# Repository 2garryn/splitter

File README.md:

# Headphone splitter

## Parts

Capacitors:
 - 470uf 25V 10x10.2 [EEEHA1E471P from Panasonic] (http://industrial.panasonic.com/ww/products/capacitors/aluminum-capacitors/aluminum-cap-smd/ha-v/EEEHA1E471P)
 - 100uf 25V 6.3x7.7 [EEEFK1E101XP from Panasonic] (http://industrial.panasonic.com/ww/products/capacitors/aluminum-capacitors/aluminum-cap-smd/fk-v/EEEFK1E101XP)
 - 4.7uf >=16V 4x5.3 or 4x5.4

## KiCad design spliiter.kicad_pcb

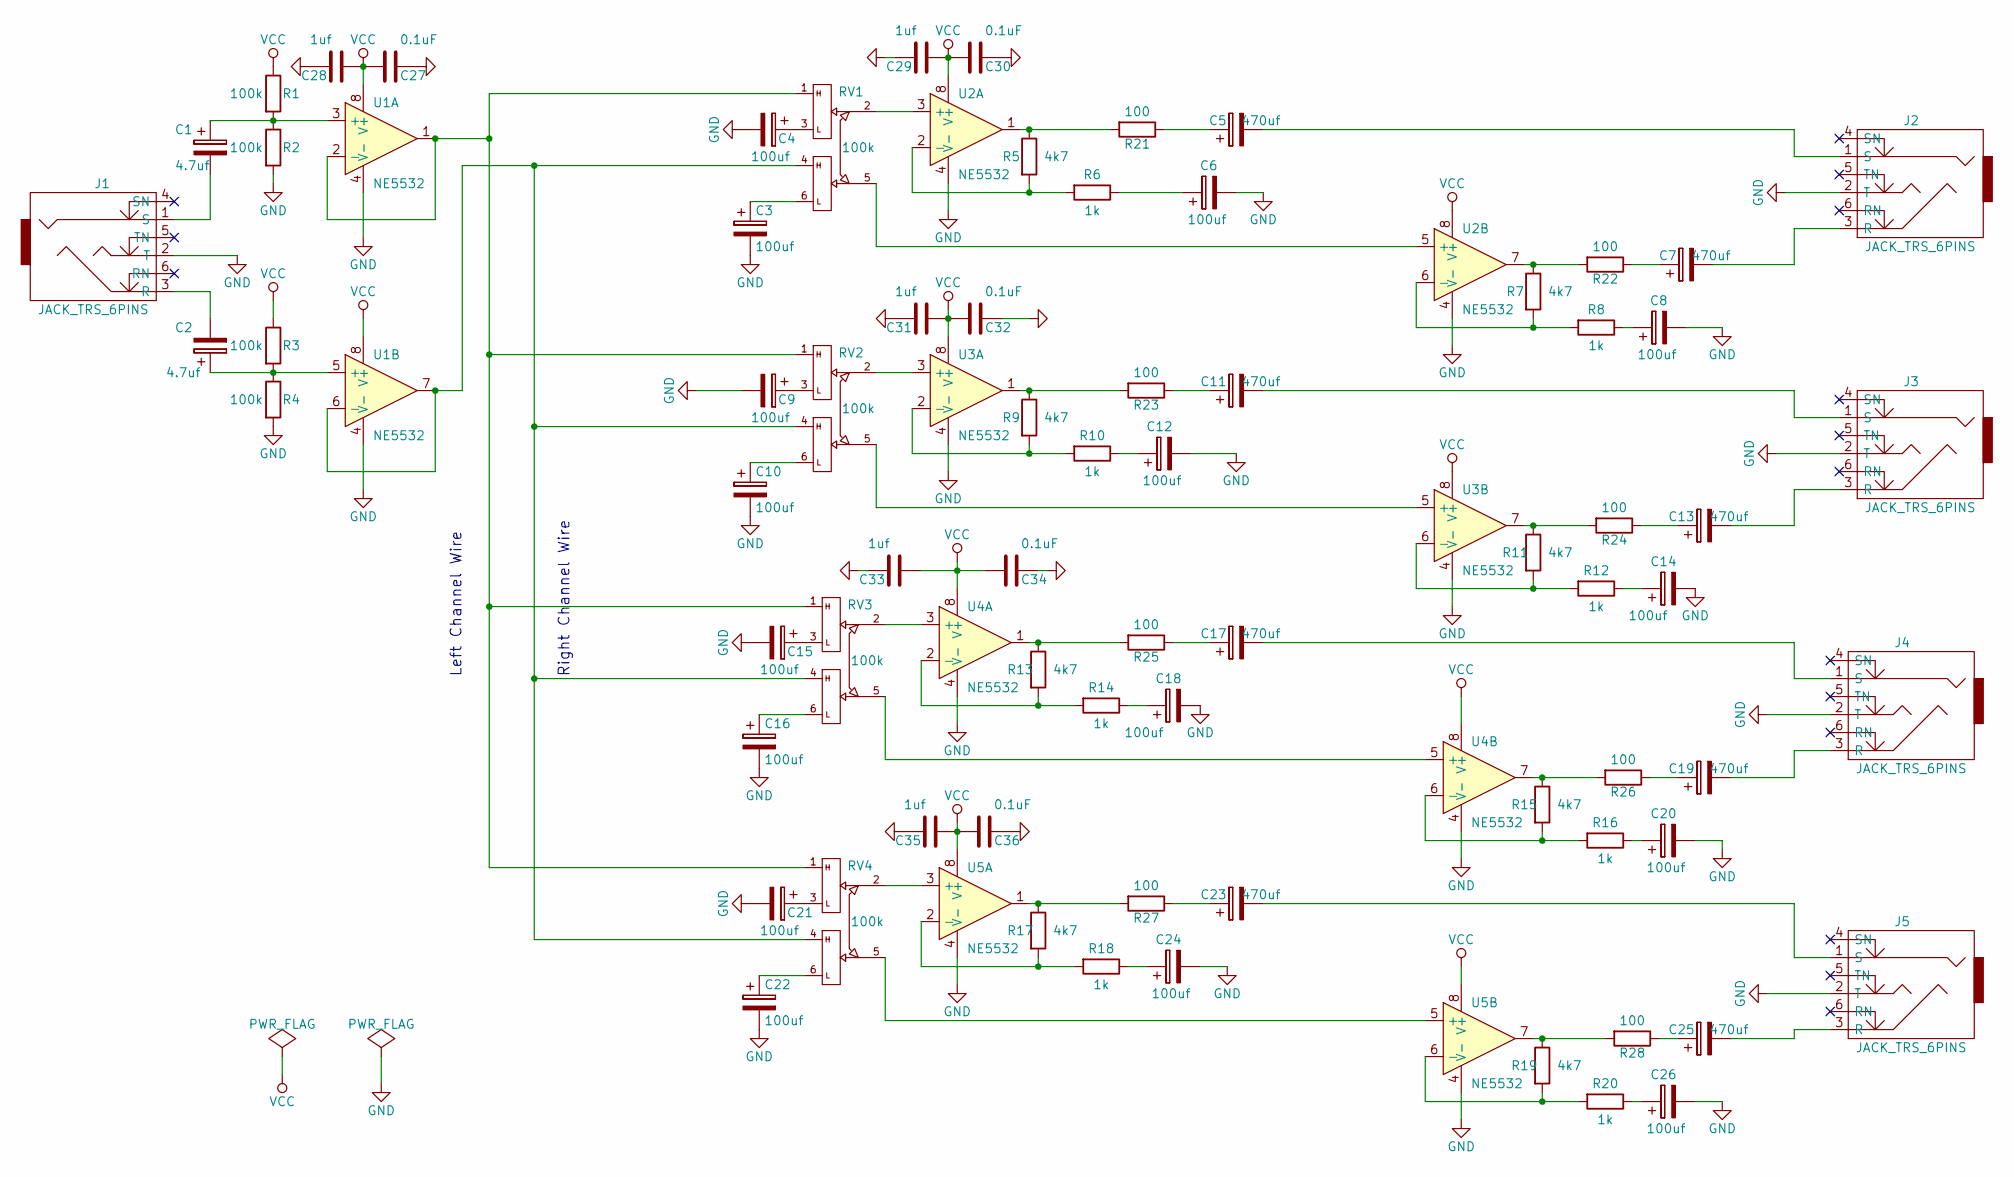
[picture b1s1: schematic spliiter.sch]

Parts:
C1, C2: 4.7uf; c_elec_4x5.3
C3, C4, C6, C8, C9, C10, C12, C14, C15, C16, C18, C20, C21, C22, C24, C26: 100uf; c_elec_6.3x7.7
C5, C7, C11, C13, C17, C19, C23, C25: 470uf; c_elec_10x10.5
C27, C30, C32, C34, C36: 0.1uF; C_0805_HandSoldering
C28, C29, C31, C33, C35: 1uf; C_0805_HandSoldering
J1, J2, J3, J4, J5: JACK_TRS_6PINS; PINHEAD1-3
R1, R2, R3, R4: 100k; R_0805_HandSoldering
R5, R7, R9, R11, R13, R15, R17, R19: 4k7; R_0805_HandSoldering
R6, R8, R10, R12, R14, R16, R18, R20: 1k; R_0805_HandSoldering
R21, R22, R23, R24, R25, R26, R27, R28: 100; R_0805_HandSoldering
RV1, RV2, RV3, RV4: 100k; PINHEAD1-6
U1, U2, U3, U4, U5: NE5532; SOIC-8_3.9x4.9mm_Pitch1.27mm

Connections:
GND: C3.2, C4.2, C6.2, C8.2, C9.2, C10.2, C12.2, C14.2, C15.2, C16.2, C18.2, C20.2, C21.2, C22.2, C24.2, C26.2, C27.1, C28.2, C29.2, C30.1, C31.2, C32.1, C33.2, C34.1, C35.2, C36.1, J1.2 (T), J2.2 (T), J3.2 (T), J4.2 (T), J5.2 (T), R2.2, R4.2, U1.4 (V-), U2.4 (V-), U3.4 (V-), U4.4 (V-), U5.4 (V-)
unnamed: C1.1, R1.2, R2.1, U1.3 (+)
unnamed: C1.2, J1.1 (S)
unnamed: C2.1, R3.2, R4.1, U1.5 (+)
unnamed: C2.2, J1.3 (R)
unnamed: C3.1, RV1.6
unnamed: C4.1, RV1.3
unnamed: C5.1, R21.1
unnamed: C5.2, J2.1 (S)
unnamed: C6.1, R6.1
unnamed: C7.1, R22.1
unnamed: C7.2, J2.3 (R)
unnamed: C8.1, R8.1
unnamed: C9.1, RV2.3
unnamed: C10.1, RV2.6
unnamed: C11.1, R23.1
unnamed: C11.2, J3.1 (S)
unnamed: C12.1, R10.1
unnamed: C13.1, R24.1
unnamed: C13.2, J3.3 (R)
unnamed: C14.1, R12.1
unnamed: C15.1, RV3.3
unnamed: C16.1, RV3.6
unnamed: C17.1, R25.1
unnamed: C17.2, J4.1 (S)
unnamed: C18.1, R14.1
unnamed: C19.1, R26.1
unnamed: C19.2, J4.3 (R)
unnamed: C20.1, R16.1
unnamed: C21.1, RV4.3
unnamed: C22.1, RV4.6
unnamed: C23.1, R27.1
unnamed: C23.2, J5.1 (S)
unnamed: C24.1, R18.1
unnamed: C25.1, R28.1
unnamed: C25.2, J5.3 (R)
unnamed: C26.1, R20.1
unnamed: R5.2, R6.2, U2.2 (-)
unnamed: R7.2, R8.2, U2.6 (-)
unnamed: R9.2, R10.2, U3.2 (-)
unnamed: R11.1, R24.2, U3.7
unnamed: R11.2, R12.2, U3.6 (-)
unnamed: R13.1, R25.2, U4.1
unnamed: R13.2, R14.2, U4.2 (-)
unnamed: R15.1, R26.2, U4.7
unnamed: R15.2, R16.2, U4.6 (-)
unnamed: R17.1, R27.2, U5.1
unnamed: R17.2, R18.2, U5.2 (-)
unnamed: R19.1, R28.2, U5.7
unnamed: R19.2, R20.2, U5.6 (-)
unnamed: R5.1, R21.2, U2.1
unnamed: R7.1, R22.2, U2.7
unnamed: R9.1, R23.2, U3.1
unnamed: RV1.1, RV2.1, RV3.1, RV4.1, U1.1, U1.2 (-)
unnamed: RV1.2, U2.3 (+)
unnamed: RV1.4, RV2.4, RV3.4, RV4.4, U1.6 (-), U1.7
unnamed: RV1.5, U2.5 (+)
unnamed: RV2.2, U3.3 (+)
unnamed: RV2.5, U3.5 (+)
unnamed: RV3.2, U4.3 (+)
unnamed: RV3.5, U4.5 (+)
unnamed: RV4.2, U5.3 (+)
unnamed: RV4.5, U5.5 (+)
VCC: C27.2, C28.1, C29.1, C30.2, C31.1, C32.2, C33.1, C34.2, C35.1, C36.2, R1.1, R3.1, U1.8 (V+), U2.8 (V+), U3.8 (V+), U4.8 (V+), U5.8 (V+)

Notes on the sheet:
Left Channel Wire
Right Channel Wire

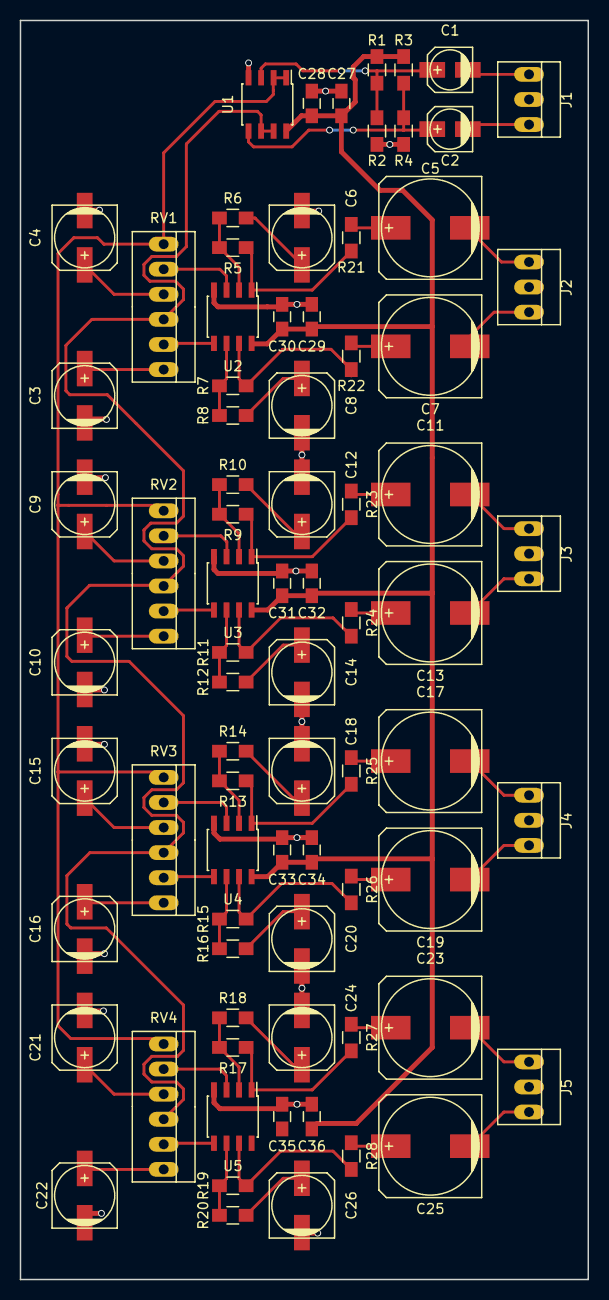
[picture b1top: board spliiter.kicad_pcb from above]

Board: 2 copper layers, 57.5 x 127.5 mm, 78 parts (0 on the bottom side), 64 nets.

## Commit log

2016-04-01 Add kicad schematic
2016-04-01 Replace +9V to VCC. Electrical rules checker passed
2016-04-02 add some values to netlist
2016-04-02 fix pinheaders
2016-04-02 add capacitors to readme
2016-04-02 add 4.7uf description
2016-04-02 fix 4.7uf description
2016-04-02 Component footprints assigned
2016-04-08 start to develop pcb
2016-06-19 pcb done
